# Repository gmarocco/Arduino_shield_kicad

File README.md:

Shield general purpose for Arduino Uno board La scheda ospita queste sezioni • E’ presente uno stadio che implementa un interruttore audio • La scheda contiene un trimmer collegato a un pin analogico della scheda Arduino • Sono presenti due pulsanti • La scheda contiene un LED RGB da 5mm • E’ presente un relè da 10 A • La scheda è predisposta per ospitare il modulo Wi-Fi ESP8266 • E’ presente un regolatore lineare che genera una tensione di 3.3V con una corrente massima di 1 A • Sono presenti due header maschio che permettono allo shield di essere collegato a una breadboard

I file di progetto sono stati realizzati con Kicad v6

English description

The board has these sections • There is a stage that implements an audio switch • The board contains a trimmer connected to an analog pin of the Arduino board • There are two buttons • The board contains a 5mm RGB LED • There is a 10 A relay • The card is designed to house the ESP8266 Wi-Fi module • There is a linear regulator that generates a voltage of 3.3V with a maximum current of 1 A • There are two male headers that allow the shield to be connected to a breadboard

The project files are made with Kicad v6

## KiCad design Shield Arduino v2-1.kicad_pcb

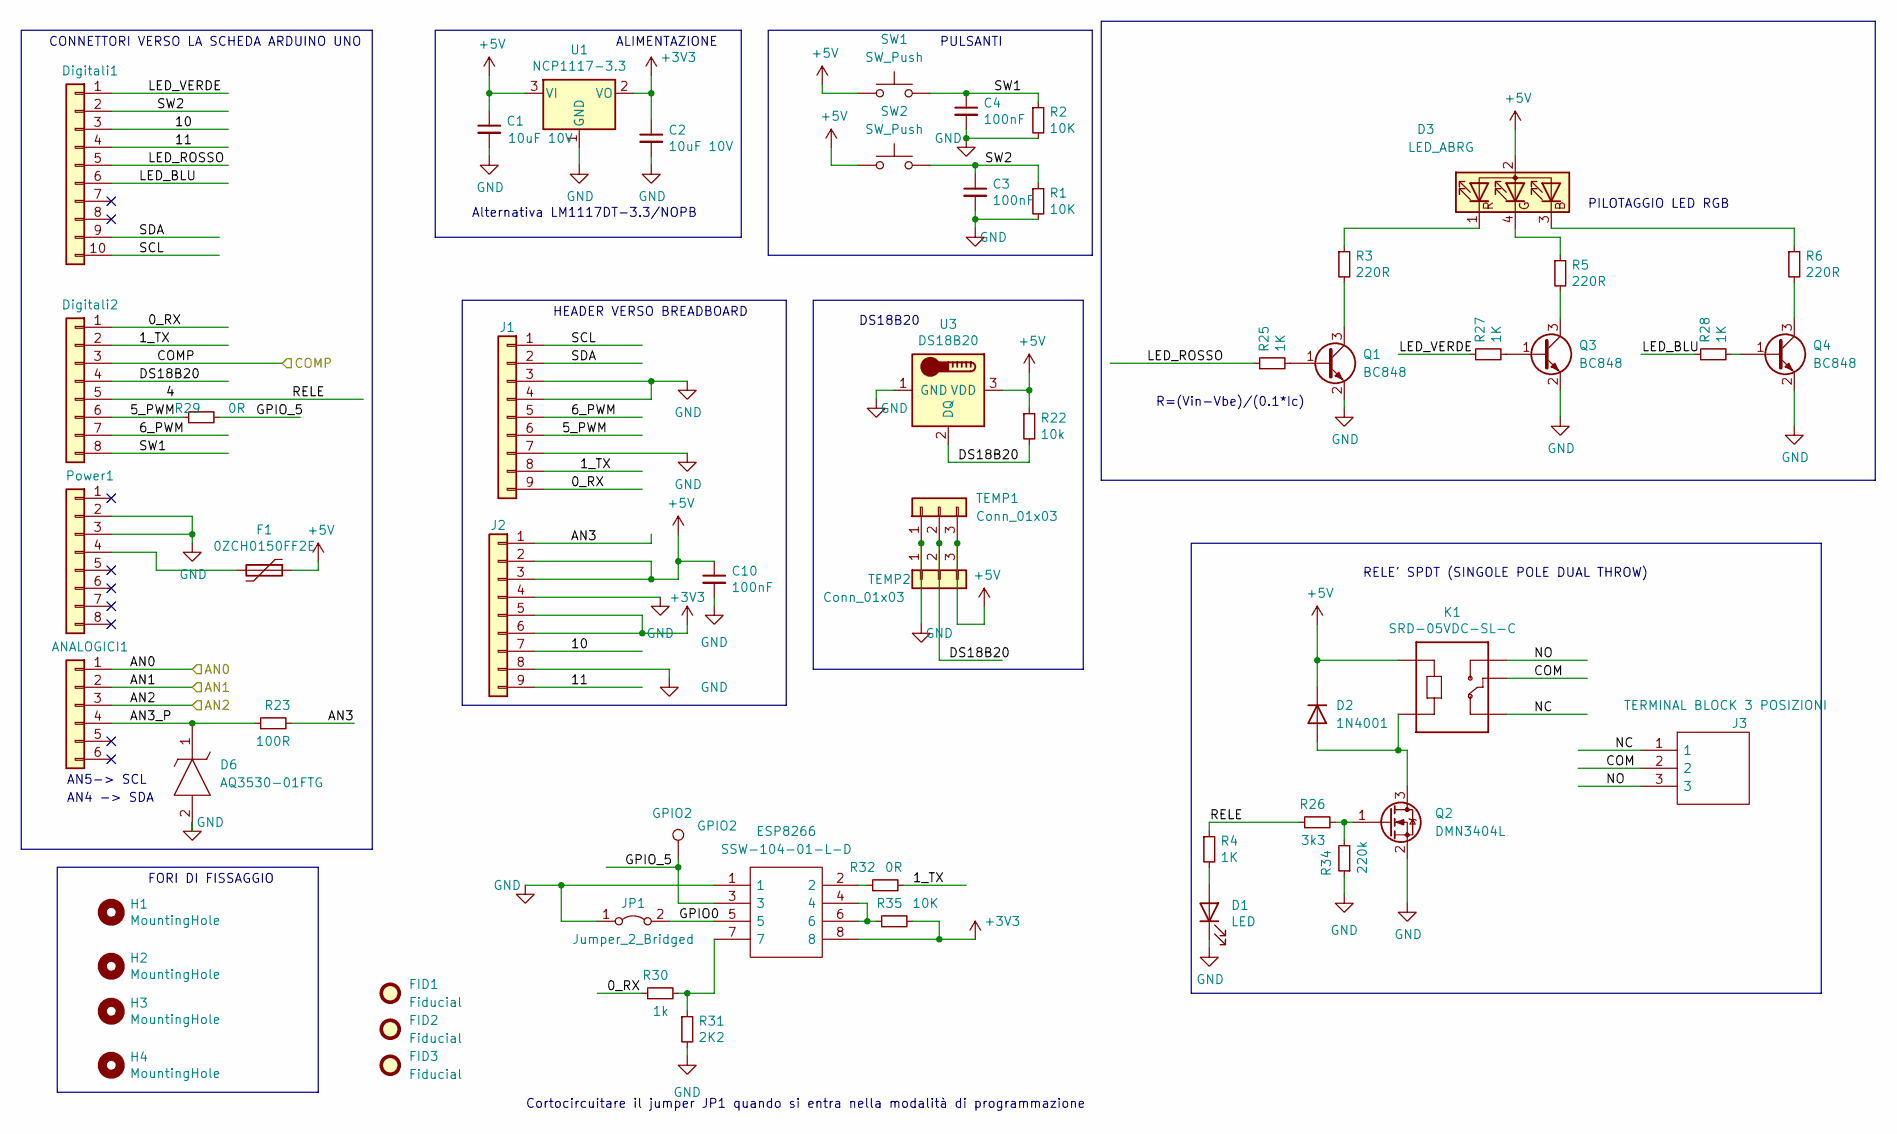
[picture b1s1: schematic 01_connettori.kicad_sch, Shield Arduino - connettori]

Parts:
ANALOGICI1: Conn_01x06; PinHeader_1x06_P2.54mm_Vertical
C1, C2: 10uF 10V; C_0805_2012Metric_Pad1.15x1.40mm_HandSolder
C3, C4: 100nF; C_0805_2012Metric_Pad1.15x1.40mm_HandSolder
C10: 100nF; C_0805_2012Metric_Pad1.18x1.45mm_HandSolder
D1: LED; LED_0805_2012Metric
D2: 1N4001; D_DO-41_SOD81_P10.16mm_Horizontal
D3: LED_ABRG; LED_D5.0mm-4_RGB
D6: AQ3530-01FTG; SOD2613X100N; Mouser Part Number 576-AQ3530-01FTG
Digitali1: Conn_01x10; PinHeader_1x10_P2.54mm_Vertical
Digitali2: Conn_01x08; PinHeader_1x08_P2.54mm_Vertical
ESP8266: SSW-104-01-L-D; RHDR8W79P254_2X4_1067X495X851P; Mouser Part Number 200-SSW10401LD
F1: 0ZCH0150FF2E; Fuse_1210_3225Metric_Pad1.42x2.65mm_HandSolder
FID1, FID2, FID3: Fiducial; Fiducial_1mm_Mask2mm
GPIO2: GPIO2; TestPoint_Pad_1.5x1.5mm
H1, H2, H3, H4: MountingHole; MountingHole_3.2mm_M3
J1, J2: Conn_01x09; PinHeader_1x09_P2.54mm_Vertical
J3: TERMINAL BLOCK 3 POSIZIONI; TB00950803BE; Mouser Part Number 571-2828373
JP1: Jumper_2_Bridged; PinHeader_1x02_P2.54mm_Vertical
K1: SRD-05VDC-SL-C; RELAY_SRD-05VDC-SL-C
Power1: Conn_01x08; PinHeader_1x08_P2.54mm_Vertical
Q1, Q3, Q4: BC848; SOT-23
Q2: DMN3404L; SOT-23
R1, R2: 10K; R_0805_2012Metric_Pad1.15x1.40mm_HandSolder
R3, R5, R6: 220R; R_0805_2012Metric_Pad1.15x1.40mm_HandSolder
R4: 1K; R_0805_2012Metric_Pad1.15x1.40mm_HandSolder
R22: 10k; R_0805_2012Metric_Pad1.15x1.40mm_HandSolder
R23: 100R; R_0805_2012Metric_Pad1.20x1.40mm_HandSolder
R25, R27, R28: 1K; R_0805_2012Metric_Pad1.20x1.40mm_HandSolder
R26: 3k3; R_0805_2012Metric_Pad1.20x1.40mm_HandSolder
R29, R32: 0R; R_0805_2012Metric_Pad1.20x1.40mm_HandSolder
R30: 1k; R_0805_2012Metric_Pad1.20x1.40mm_HandSolder
R31: 2K2; R_0805_2012Metric_Pad1.20x1.40mm_HandSolder
R34: 220k; R_0805_2012Metric_Pad1.20x1.40mm_HandSolder
R35: 10K; R_0805_2012Metric_Pad1.20x1.40mm_HandSolder
SW1, SW2: SW_Push; SW_PUSH_6mm_H4.3mm
TEMP1, TEMP2: Conn_01x03; PinSocket_1x03_P2.54mm_Vertical
U1: NCP1117-3.3; TO-252-2
U3: DS18B20; TO-92_Inline

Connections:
+3V3: C2.1, ESP8266.8, J2.5, J2.6, R35.2, U1.2 (VO)
+5V: C1.1, C10.1, D2.1 (K), D3.2 (A), F1.1, J2.2, J2.3, K1.A1, R22.1, SW1.1, SW2.1, TEMP1.3, TEMP2.3, U1.3 (VI), U3.3 (VDD); also elsewhere on the board
/01_connettori/0_RX: Digitali2.1, J1.9, R30.1
/01_connettori/1_TX: Digitali2.2, J1.8, R32.2
/01_connettori/4: Digitali2.5, R4.1, R26.1
/01_connettori/5_PWM: Digitali2.6, J1.6, R29.1
/01_connettori/6_PWM: Digitali2.7, J1.5
/01_connettori/10: Digitali1.3, J2.7
/01_connettori/11: Digitali1.4, J2.9
/01_connettori/AN0: ANALOGICI1.1; also elsewhere on the board
/01_connettori/AN1: ANALOGICI1.2; also elsewhere on the board
/01_connettori/AN2: ANALOGICI1.3; also elsewhere on the board
/01_connettori/AN3: J2.1, R23.2
/01_connettori/AN3_P: ANALOGICI1.4, D6.1, R23.1
/01_connettori/COM: J3.2, K1.COM
/01_connettori/COMP: Digitali2.3; also elsewhere on the board
/01_connettori/DS18B20: Digitali2.4, R22.2, TEMP1.2, TEMP2.2, U3.2 (DQ)
/01_connettori/GPIO0: ESP8266.5, JP1.2 (B)
/01_connettori/GPIO_5: ESP8266.3, GPIO2.1, R29.2
/01_connettori/LED_BLU: Digitali1.6, R28.1
/01_connettori/LED_ROSSO: Digitali1.5, R25.1
/01_connettori/LED_VERDE: Digitali1.1, R27.1
/01_connettori/NC: J3.1, K1.NC
/01_connettori/NO: J3.3, K1.NO
/01_connettori/SCL: Digitali1.10, J1.1
/01_connettori/SDA: Digitali1.9, J1.2
/01_connettori/SW1: C4.1, Digitali2.8, R2.1, SW1.2
/01_connettori/SW2: C3.1, Digitali1.2, R1.1, SW2.2
GND: C1.2, C2.2, C3.2, C4.2, C10.2, D1.1 (K), D6.2, ESP8266.1, J1.3, J1.4, J1.7, J2.4, J2.8, JP1.1 (A), Power1.2, Power1.3, Q1.2 (E), Q2.2 (S), Q3.2 (E), Q4.2 (E), R1.2, R2.2, R31.2, R34.1, TEMP1.1, TEMP2.1, U1.1 (GND), U3.1 (GND); also elsewhere on the board
unnamed: D1.2 (A), R4.2
unnamed: D2.2 (A), K1.A2, Q2.3 (D)
unnamed: D3.1 (RK), R3.1
unnamed: D3.3 (BK), R6.1
unnamed: D3.4 (GK), R5.1
unnamed: ESP8266.2, R32.1
unnamed: ESP8266.4, ESP8266.6, R35.1
unnamed: ESP8266.7, R30.2, R31.1
unnamed: F1.2, Power1.4
unnamed: Q1.1 (B), R25.2
unnamed: Q1.3 (C), R3.2
unnamed: Q2.1 (G), R26.2, R34.2
unnamed: Q3.1 (B), R27.2
unnamed: Q3.3 (C), R5.2
unnamed: Q4.1 (B), R28.2
unnamed: Q4.3 (C), R6.2

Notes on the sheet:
DS18B20
CONNETTORI VERSO LA SCHEDA ARDUINO UNO
HEADER VERSO BREADBOARD
FORI DI FISSAGGIO
PILOTAGGIO LED RGB
PULSANTI
AN4 -> SDA
AN5-> SCL
RELE' SPDT (SINGOLE POLE DUAL THROW)
R=(Vin-Vbe)/(0.1*Ic)
Cortocircuitare il jumper JP1 quando si entra nella modalità di programmazione
ALIMENTAZIONE
Alternativa LM1117DT-3.3/NOPB

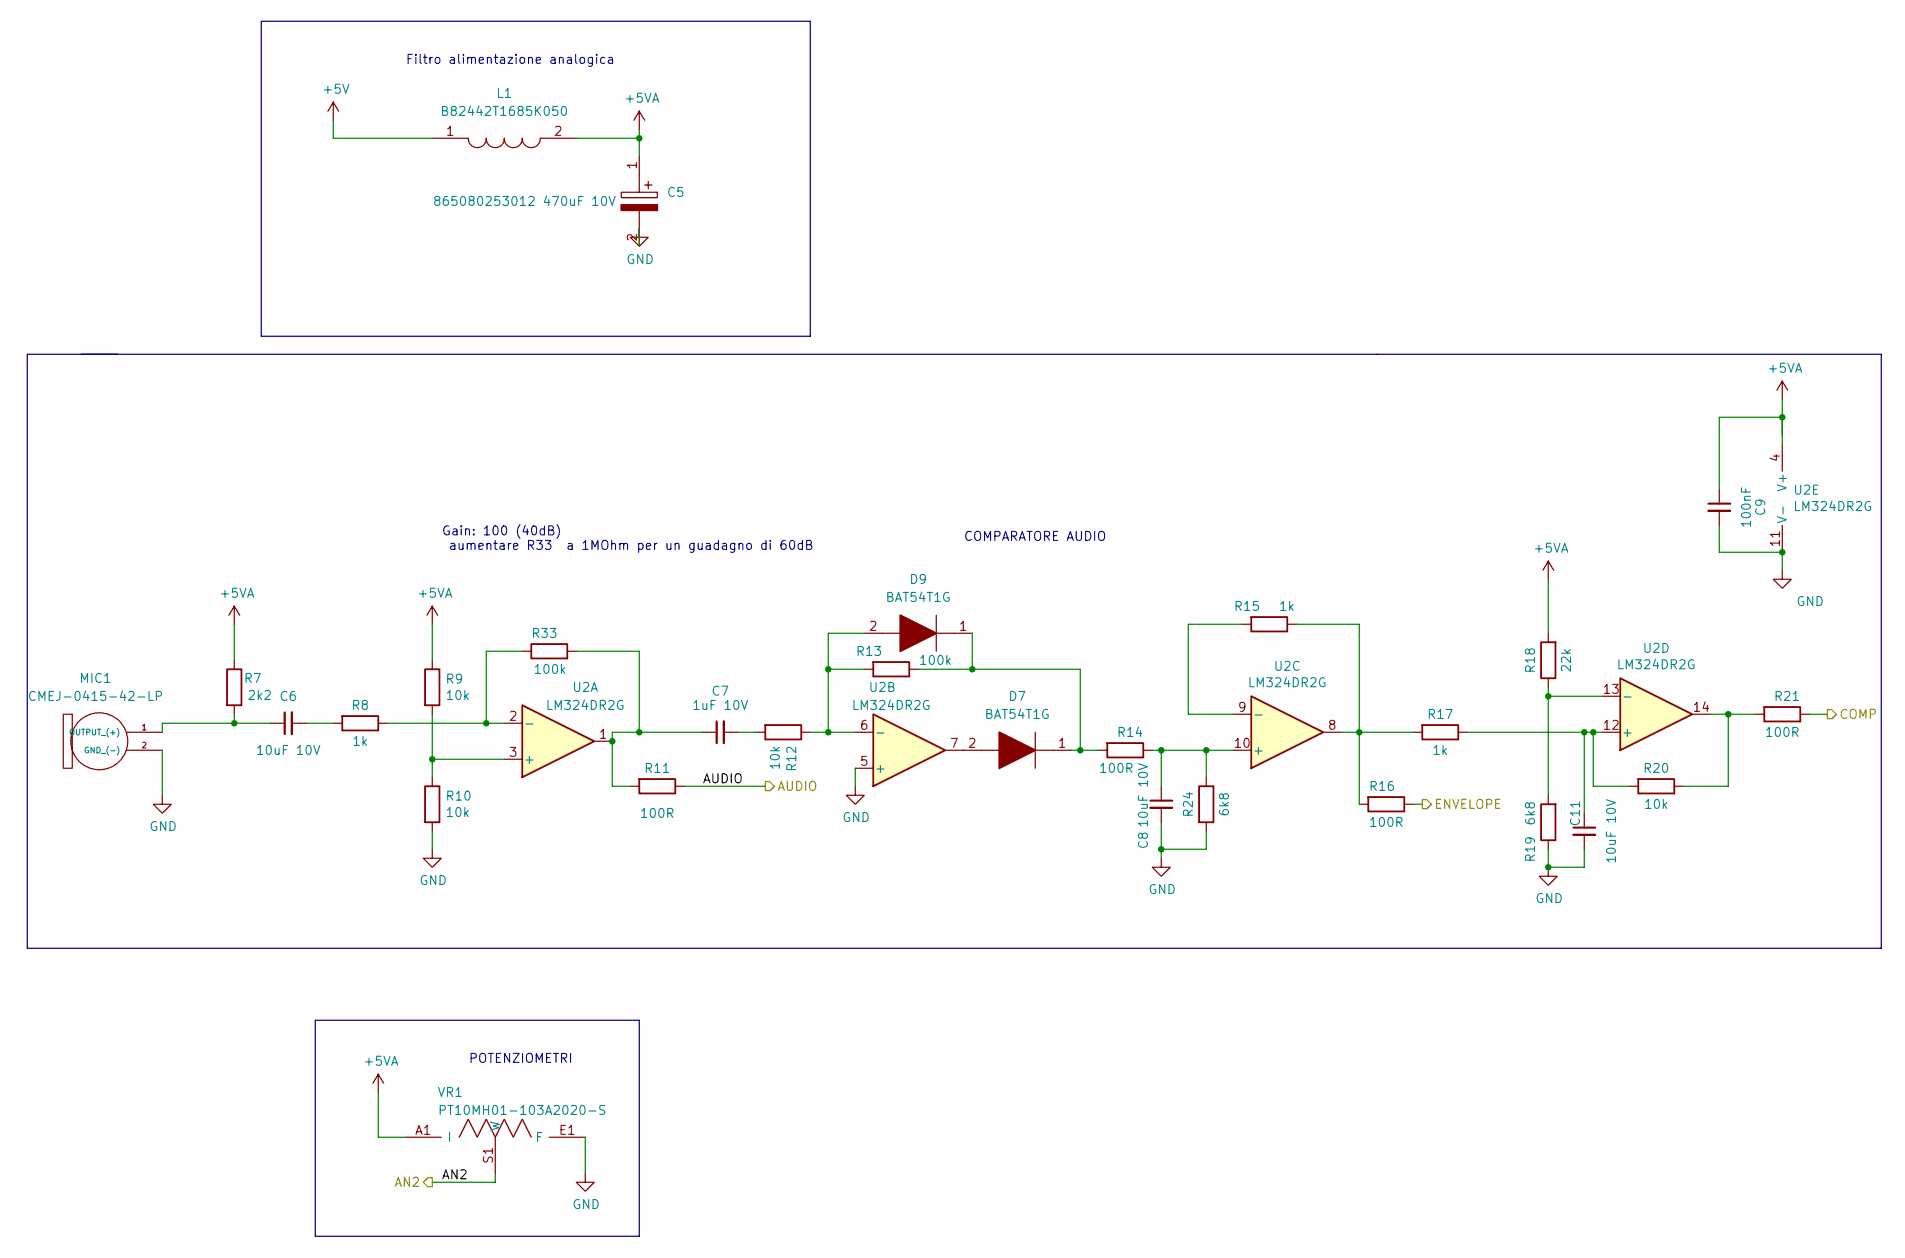
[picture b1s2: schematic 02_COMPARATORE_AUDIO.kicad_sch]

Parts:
C5: 865080253012 470uF 10V; CP_Elec_8x6.2; Mouser Part Number 710-875105244013
C6, C8: 10uF 10V; C_0805_2012Metric_Pad1.15x1.40mm_HandSolder
C7: 1uF 10V; C_0805_2012Metric_Pad1.15x1.40mm_HandSolder
C9: 100nF; C_0805_2012Metric_Pad1.15x1.40mm_HandSolder
C11: 10uF 10V; C_0805_2012Metric_Pad1.18x1.45mm_HandSolder
D7, D9: BAT54T1G; SOD3716X135N; Mouser Part Number 863-BAT54T1G
L1: B82442T1685K050; INDPM5850X530N; Mouser Part Number 871-B82442T1685K050
MIC1: CMEJ-0415-42-LP; CMEJ041542LP; Mouser Part Number 490-CMEJ-0415-42-LP
R7: 2k2; R_0805_2012Metric_Pad1.15x1.40mm_HandSolder
R8, R15, R17: 1k; R_0805_2012Metric_Pad1.15x1.40mm_HandSolder
R9, R10, R12, R20: 10k; R_0805_2012Metric_Pad1.15x1.40mm_HandSolder
R11, R14, R16, R21: 100R; R_0805_2012Metric_Pad1.15x1.40mm_HandSolder
R13: 100k; R_0805_2012Metric_Pad1.15x1.40mm_HandSolder
R18: 22k; R_0805_2012Metric_Pad1.15x1.40mm_HandSolder
R19: 6k8; R_0805_2012Metric_Pad1.15x1.40mm_HandSolder
R24: 6k8; R_0805_2012Metric_Pad1.20x1.40mm_HandSolder
R33: 100k; R_0805_2012Metric_Pad1.20x1.40mm_HandSolder
U2: LM324DR2G; SOIC-14_3.9x8.7mm_P1.27mm
VR1: PT10MH01-103A2020-S; PT10MH01103A2020S; Mouser Part Number 531-PT10MH-10K-S

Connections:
+5V: L1.1; also elsewhere on the board
+5VA: C5.1, C9.1, L1.2, R7.1, R9.1, R18.2, U2.4 (V+), VR1.A1 (I)
/01_connettori/AN0: R11.1; also elsewhere on the board
/01_connettori/AN1: R16.1; also elsewhere on the board
/01_connettori/AN2: VR1.S1 (W); also elsewhere on the board
/01_connettori/COMP: R21.1; also elsewhere on the board
GND: C5.2, C8.2, C9.2, C11.2, MIC1.2 (GND_(-)), R10.2, R19.1, R24.2, U2.5 (+), U2.11 (V-), VR1.E1 (F); also elsewhere on the board
unnamed: C6.1, MIC1.1 (OUTPUT_(+)), R7.2
unnamed: C6.2, R8.2
unnamed: C7.1, R11.2, R33.2, U2.1
unnamed: C7.2, R12.2
unnamed: C8.1, R14.1, R24.1, U2.10 (+)
unnamed: C11.1, R17.1, R20.2, U2.12 (+)
unnamed: D7.1, D9.1, R13.1, R14.2
unnamed: D7.2, U2.7
unnamed: D9.2, R12.1, R13.2, U2.6 (-)
unnamed: R9.2, R10.1, U2.3 (+)
unnamed: R15.1, R16.2, R17.2, U2.8
unnamed: R15.2, U2.9 (-)
unnamed: R18.1, R19.2, U2.13 (-)
unnamed: R20.1, R21.2, U2.14
unnamed: R8.1, R33.1, U2.2 (-)

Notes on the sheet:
Filtro alimentazione analogica
POTENZIOMETRI
Gain: 100 (40dB) aumentare R33 a 1MOhm per un guadagno di 60dB
COMPARATORE AUDIO

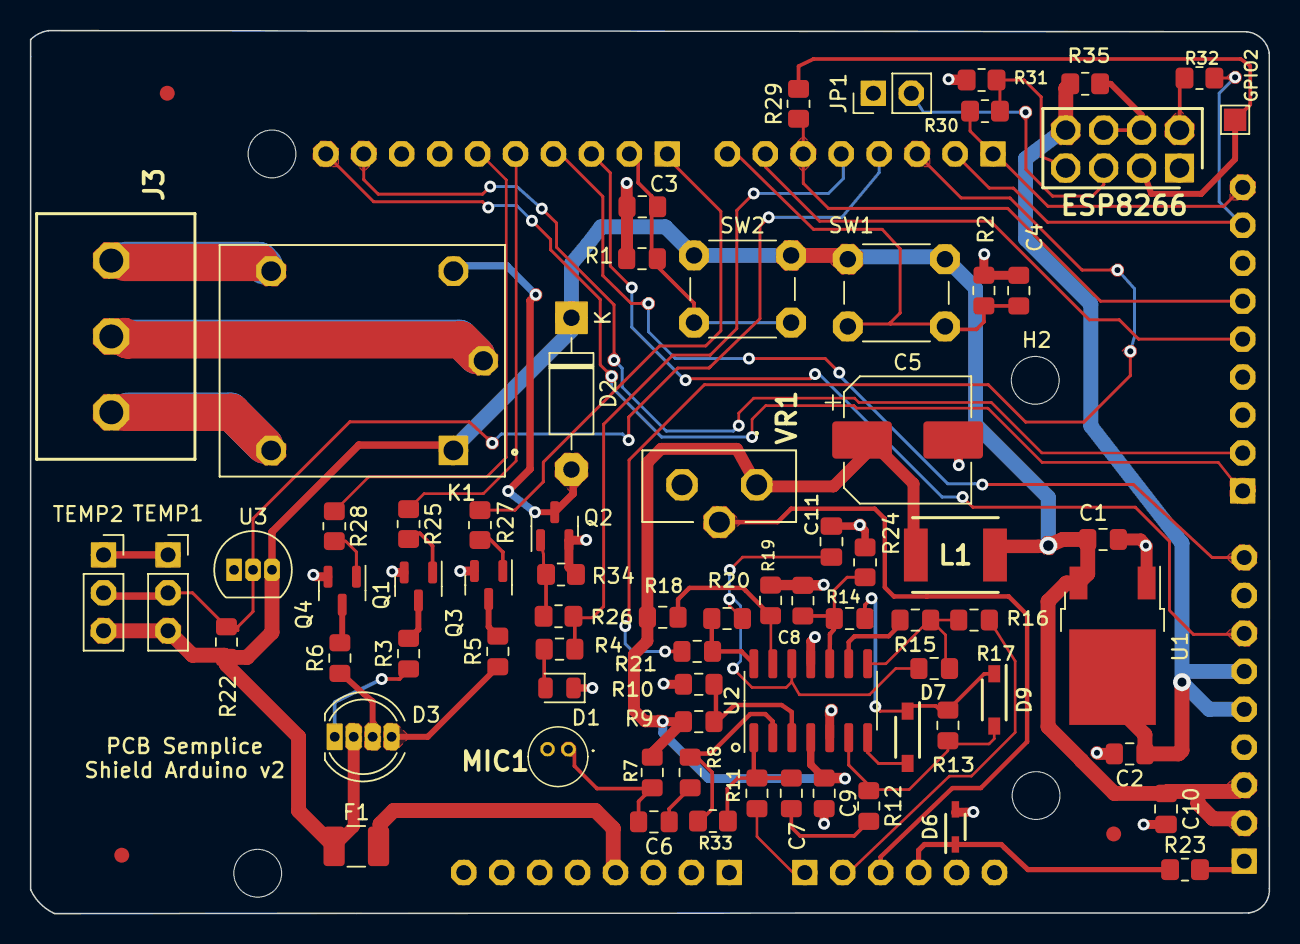
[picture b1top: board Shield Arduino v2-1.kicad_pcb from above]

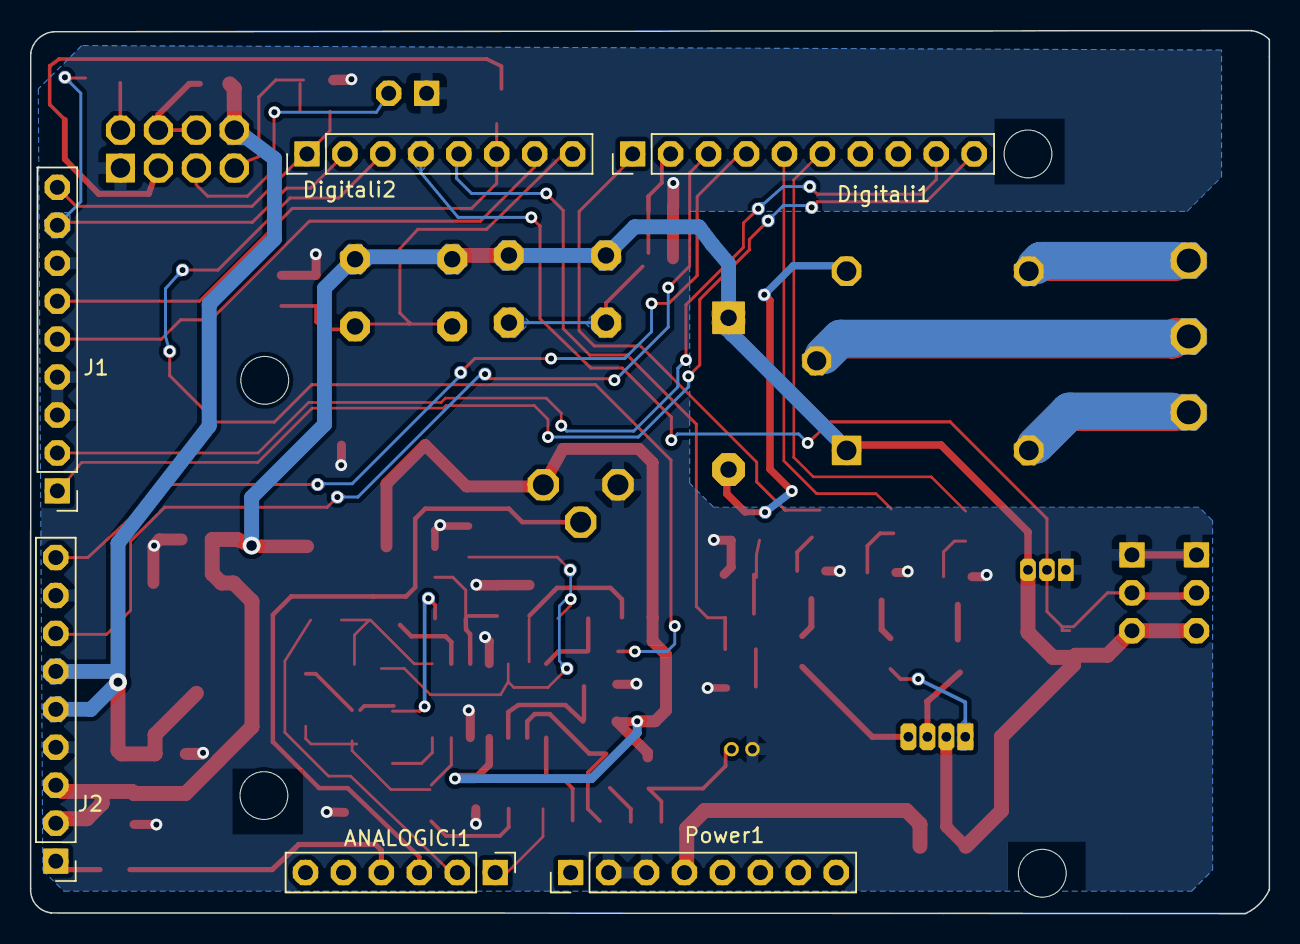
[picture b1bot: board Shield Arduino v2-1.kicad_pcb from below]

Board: 2 copper layers, 82.9 x 59.1 mm, 85 parts (6 on the bottom side), 61 nets.

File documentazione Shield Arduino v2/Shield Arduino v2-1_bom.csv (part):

"Source:","C:\Users\pc\Documents\progetto PCB semplice\3° versione Kicad\live\Shield Arduino v2-1\Shield Arduino v2-1.kicad_sch"
"Date:","26/06/2022 13:20:24"
"Tool:","Eeschema (6.0.6)"
"Generator:","C:\Program Files\KiCad\6.0\bin\scripting\plugins/bom_csv_grouped_by_value.py"
"Component Count:","84"

"Individual Components:"

"Item","Qty","Reference(s)","Value","LibPart","Footprint","Datasheet","Description","Height","MANUFACTURER","Manufacturer_Name","Manufacturer_Part_Number","Mouser Part Number","Mouser Price/Stock","STANDARD"
"","","ANALOGICI1","Conn_01x06","Connector_Generic:Conn_01x06","Connector_PinHeader_2.54mm:PinHeader_1x06_P2.54mm_Vertical","~","","","","","","","",""
"","","C1","10uF 10V","Device:C_Small","Capacitor_SMD:C_0805_2012Metric_Pad1.15x1.40mm_HandSolder","~","","","","","","","",""
"","","C2","10uF 10V","Device:C_Small","Capacitor_SMD:C_0805_2012Metric_Pad1.15x1.40mm_HandSolder","~","","","","","","","",""
"","","C3","100nF","Device:C_Small","Capacitor_SMD:C_0805_2012Metric_Pad1.15x1.40mm_HandSolder","~","","","","","","","",""
"","","C4","100nF","Device:C_Small","Capacitor_SMD:C_0805_2012Metric_Pad1.15x1.40mm_HandSolder","~","","","","","","","",""
"","","C5","865080253012 470uF 10V","SamacSys_lib:875105244013","Capacitor_SMD:CP_Elec_8x6.2","https://www.we-online.com/catalog/datasheet/875105244013.pdf","Wurth Elektronik 470uF Polymer Capacitor 10V dc Surface Mount -865080253012","5.8","","Wurth Elektronik","875105244013","710-875105244013","https://www.mouser.co.uk/ProductDetail/Wurth-Elektronik/8751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",""
"","","C6","10uF 10V","Device:C_Small","Capacitor_SMD:C_0805_2012Metric_Pad1.15x1.40mm_HandSolder","~","","","","","","","",""
"","","C7","1uF 10V","Device:C_Small","Capacitor_SMD:C_0805_2012Metric_Pad1.15x1.40mm_HandSolder","~","","","","","","","",""
"","","C8","10uF 10V","Device:C_Small","Capacitor_SMD:C_0805_2012Metric_Pad1.15x1.40mm_HandSolder","~","","","","","","","",""
"","","C9","100nF","Device:C_Small","Capacitor_SMD:C_0805_2012Metric_Pad1.15x1.40mm_HandSolder","~","","","","","","","",""
"","","C10","100nF","Device:C_Small","Capacitor_SMD:C_0805_2012Metric_Pad1.18x1.45mm_HandSolder","~","","","","","","","",""
"","","C11","10uF 10V","Device:C_Small","Capacitor_SMD:C_0805_2012Metric_Pad1.18x1.45mm_HandSolder","~","","","","","","","",""
"","","D1","LED","Device:LED","LED_SMD:LED_0805_2012Metric","~","","","","","","","",""
"","","D2","1N4001","Diode:1N4001","Diode_THT:D_DO-41_SOD81_P10.16mm_Horizontal","http://www.vishay.com/docs/88503/1n4001.pdf","","","","","","","",""
"","","D3","LED_ABRG","Device:LED_ABRG","LED_THT:LED_D5.0mm-4_RGB","~","","","","","","","",""
"","","D6","AQ3530-01FTG","SamacSys_lib:AQ3530-01FTG","SOD2613X100N","https://www.littelfuse.com/~/media/electronics/datasheets/tv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","0.3pF 22kV unidirectional TVS diode","1","","LITTELFUSE","AQ3530-01FTG","576-AQ3530-01FTG","https://www.mouser.co.uk/ProductDetail/Littelfuse/AQ3530-01F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",""
"","","D7","BAT54T1G","LIBRARY LOADER_AUTO:BAT54T1G","SOD3716X135N","http://www.onsemi.com/pub/Collateral/BAT54T1-D.PDF","","1.35","","onsemi","BAT54T1G","863-BAT54T1G","https://www.mouser.co.uk/ProductDetail/onsemi/BAT54T1G?qs=vL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",""
"","","D9","BAT54T1G","LIBRARY LOADER_AUTO:BAT54T1G","SOD3716X135N","http://www.onsemi.com/pub/Collateral/BAT54T1-D.PDF","","1.35","","onsemi","BAT54T1G","863-BAT54T1G","https://www.mouser.co.uk/ProductDetail/onsemi/BAT54T1G?qs=vL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",""
"","","Digitali1","Conn_01x10","Connector_Generic:Conn_01x10","Connector_PinHeader_2.54mm:PinHeader_1x10_P2.54mm_Vertical","~","","","","","","","",""
"","","Digitali2","Conn_01x08","Connector_Generic:Conn_01x08","Connector_PinHeader_2.54mm:PinHeader_1x08_P2.54mm_Vertical","~","","","","","","","",""
"","","ESP8266","SSW-104-01-L-D","SamacSys_Parts:SSW-104-01-L-D","RHDR8W79P254_2X4_1067X495X851P","http://suddendocs.samtec.com/prints/ssw-1xx-xx-xxx-x-xx-xxx-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","8 Position, .100&quot; Tiger Buy&trade; Socket Strip","8.51","","SAMTEC","SSW-104-01-L-D","200-SSW10401LD","https://www.mouser.co.uk/ProductDetail/Samtec/SSW-104-01-L-D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",""
"","","F1","0ZCH0150FF2E","Device:Polyfuse","Fuse:Fuse_1210_3225Metric_Pad1.42x2.65mm_HandSolder","~","","","","","","","",""
"","","FID1","Fiducial","Mechanical:Fiducial","Fiducial:Fiducial_1mm_Mask2mm","~","","","","","","","",""
"","","FID2","Fiducial","Mechanical:Fiducial","Fiducial:Fiducial_1mm_Mask2mm","~","","","","","","","",""
"","","FID3","Fiducial","Mechanical:Fiducial","Fiducial:Fiducial_1mm_Mask2mm","~","","","","","","","",""
"","","GPIO2","GPIO2","Connector:TestPoint","TestPoint:TestPoint_Pad_1.5x1.5mm","~","","","","","","","",""
"","","H1","MountingHole","Mechanical:MountingHole","MountingHole:MountingHole_3.2mm_M3","~","","","","","","","",""
"","","H2","MountingHole","Mechanical:MountingHole","MountingHole:MountingHole_3.2mm_M3","~","","","","","","","",""
"","","H3","MountingHole","Mechanical:MountingHole","MountingHole:MountingHole_3.2mm_M3","~","","","","","","","",""
"","","H4","MountingHole","Mechanical:MountingHole","MountingHole:MountingHole_3.2mm_M3","~","","","","","","","",""
"","","J1","Conn_01x09","Connector_Generic:Conn_01x09","Connector_PinHeader_2.54mm:PinHeader_1x09_P2.54mm_Vertical","~","","","","","","","",""
"","","J2","Conn_01x09","Connector_Generic:Conn_01x09","Connector_PinHeader_2.54mm:PinHeader_1x09_P2.54mm_Vertical","~","","","","","","","",""
"","","J3","TERMINAL BLOCK 3 POSIZIONI","SamacSys_Parts:282837-3","LibraryLoaderAuto:TB00950803BE","","Fixed Terminal Blocks 5.08MM PCB MOUNT 3P","10.3","","TE Connectivity","282837-3","571-2828373","https://www.mouser.co.uk/ProductDetail/TE-Connectivity/28283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",""
"","","JP1","Jumper_2_Bridged","Jumper:Jumper_2_Bridged","Connector_PinHeader_2.54mm:PinHeader_1x02_P2.54mm_Vertical","~","","","","","","","",""
"","","K1","SRD-05VDC-SL-C","SRD-05VDC-SL-C:SRD-05VDC-SL-C","RELAY_SRD-05VDC-SL-C","","","","SONGLE RELAY","","","","","IPC-7251"
"","","L1","B82442T1685K050","SamacSys_lib:B82442T1685K050","INDPM5850X530N","https://componentsearchengine.com/Datasheets/1/B82442T1685K050.pdf","SMD / SMT Inductors (Coils), L=6800uH, 5.6mm x 5.0mm [EIA 2220]","5.3","","TDK","B82442T1685K050","871-B82442T1685K050","http://www.mouser.com/Search/ProductDetail.aspx?qs=x3Z3Taiyc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",""
"","","MIC1","CMEJ-0415-42-LP","LibraryLoader:CMEJ-0415-42-LP","LibraryLoaderAuto:CMEJ041542LP","https://componentsearchengine.com/Datasheets/1/CMEJ-0415-42-LP.pdf","Microphones microphone, 4 mm, electret condenser, omnidirectional, Long Pin, 2 Vdc, 42 dB sensitivity","2","","CUI Inc.","CMEJ-0415-42-LP","490-CMEJ-0415-42-LP","https://www.mouser.co.uk/ProductDetail/CUI-Devices/CMEJ-0415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",""
"","","Power1","Conn_01x08","Connector_Generic:Conn_01x08","Connector_PinHeader_2.54mm:PinHeader_1x08_P2.54mm_Vertical","~","","","","","","","",""
"","","Q1","BC848","Transistor_BJT:BC848","Package_TO_SOT_SMD:SOT-23","http://www.infineon.com/dgdl/Infineon-BC847SERIES_BC848SERIE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","","","","","","","",""
"","","Q2","DMN3404L","Transistor_FET:DMN3404L","Package_TO_SOT_SMD:SOT-23","http://www.diodes.com/assets/Datasheets/ds31787.pdf","","","","","","","",""
"","","Q3","BC848","Transistor_BJT:BC848","Package_TO_SOT_SMD:SOT-23","http://www.infineon.com/dgdl/Infineon-BC847SERIES_BC848SERIE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","","","","","","","",""
"","","Q4","BC848","Transistor_BJT:BC848","Package_TO_SOT_SMD:SOT-23","http://www.infineon.com/dgdl/Infineon-BC847SERIES_BC848SERIE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","","","","","","","",""
"","","R1","10K","Device:R_Small","Resistor_SMD:R_0805_2012Metric_Pad1.15x1.40mm_HandSolder","~","","","","","","","",""
"","","R2","10K","Device:R_Small","Resistor_SMD:R_0805_2012Metric_Pad1.15x1.40mm_HandSolder","~","","","","","","","",""
"","","R3","220R","Device:R_Small","Resistor_SMD:R_0805_2012Metric_Pad1.15x1.40mm_HandSolder","~","","","","","","","",""
"","","R4","1K","Device:R_Small","Resistor_SMD:R_0805_2012Metric_Pad1.15x1.40mm_HandSolder","~","","","","","","","",""
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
